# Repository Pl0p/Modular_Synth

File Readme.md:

# Welcome here =)

Here you can find all the resources I use to build my modules.
You will also find my modules, their Kicad files, their schematics as well as my sources of inspiration and pictures/videos of the prototypes and finished modules

You will also find

## [A big list of open-source/open-hardware builders](https://github.com/Pl0p/Modular_Synth/blob/main/List_of_open-source_makers.md)
All modules in the list are not necessarily in eurorack format, but all have their schematics available if not more

And 

### [A list (in progress) of modules by category](https://github.com/Pl0p/Modular_Synth/blob/main/List_of_modules_by_functions.md)
These are the module's files and descriptions available in the list above but classified by category

Don't hesitate to participate if you find other sources of music/video schematics

Thing you can do to help :
- Class thing in alphabetical order for the Open-hardware-builders list
- Add new entry
- Take a look at the modules by category and continue to class them
- Look for typos
- Have a good day =)

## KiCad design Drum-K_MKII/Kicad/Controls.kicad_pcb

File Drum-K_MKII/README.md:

# Drum K MkII
Analogue drum kick

## Controls are :

 - Transient shape
 - Decay
 - Tune
 - Tone
 - Distortion

### Inputs

 - Trigger
 - Decay CV (vactrol)
 - Accent

# [Here is the schematic](https://github.com/Pl0p/Modular_Synth/blob/main/Drum-K_MKII/Drum-K_MKII.pdf)

### Main PCB 

### Front Panel

### Sandwich

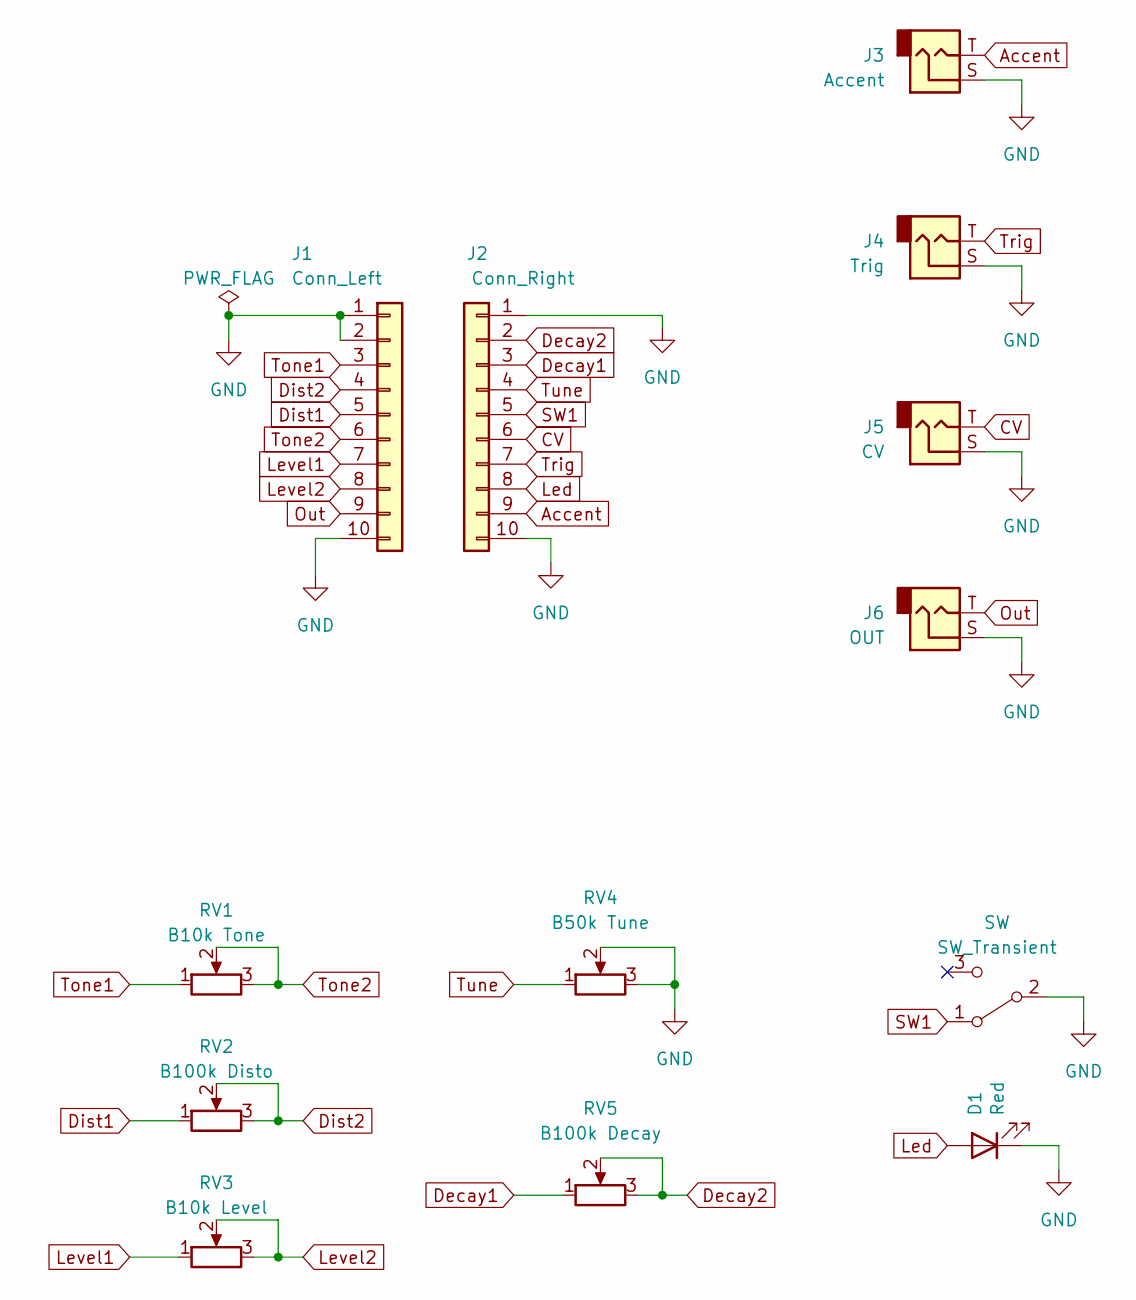
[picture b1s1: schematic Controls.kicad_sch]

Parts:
D1: Red; LED_D5.0mm
J1: Conn_Left; PinHeader_1x10
J2: Conn_Right; PinHeader_1x10
J3: Accent; Jack_3.5mm_Vertical
J4: Trig; Jack_3.5mm_Vertical
J5: CV; Jack_3.5mm_Vertical
J6: OUT; Jack_3.5mm_Vertical
RV1: B10k Tone; Potentiometer_Alps_RK09L_Single_Vertical
RV2: B100k Disto; Potentiometer_Alps_RK09L_Single_Vertical
RV3: B10k Level; Potentiometer_Alps_RK09L_Single_Vertical
RV4: B50k Tune; Potentiometer_Alps_RK09L_Single_Vertical
RV5: B100k Decay; Potentiometer_Alps_RK09L_Single_Vertical
SW: SW_Transient

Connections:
Accent: J2.9, J3.T
CV: J2.6, J5.T
Decay1: J2.3, RV5.1
Decay2: J2.2, RV5.2, RV5.3
Dist1: J1.5, RV2.1
Dist2: J1.4, RV2.2, RV2.3
GND: D1.1 (K), J1.1, J1.2, J1.10, J2.1, J2.10, J3.S, J4.S, J5.S, J6.S, RV4.2, RV4.3; also elsewhere on the board
Led: D1.2 (A), J2.8
Level1: J1.7, RV3.1
Level2: J1.8, RV3.2, RV3.3
Out: J1.9, J6.T
SW1: J2.5, J6.5, SW.1 (A); also elsewhere on the board
Tone1: J1.3, RV1.1
Tone2: J1.6, RV1.2, RV1.3
Trig: J2.7, J4.T
Tune: J2.4, RV4.1

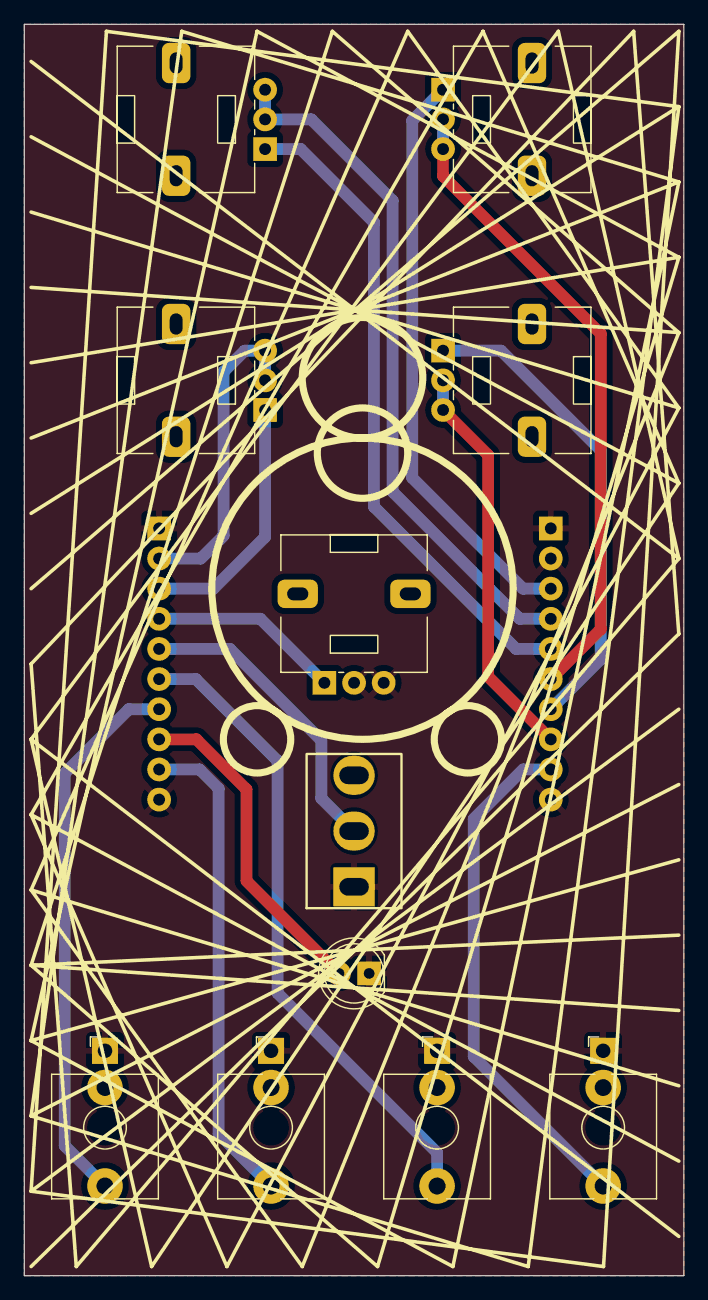
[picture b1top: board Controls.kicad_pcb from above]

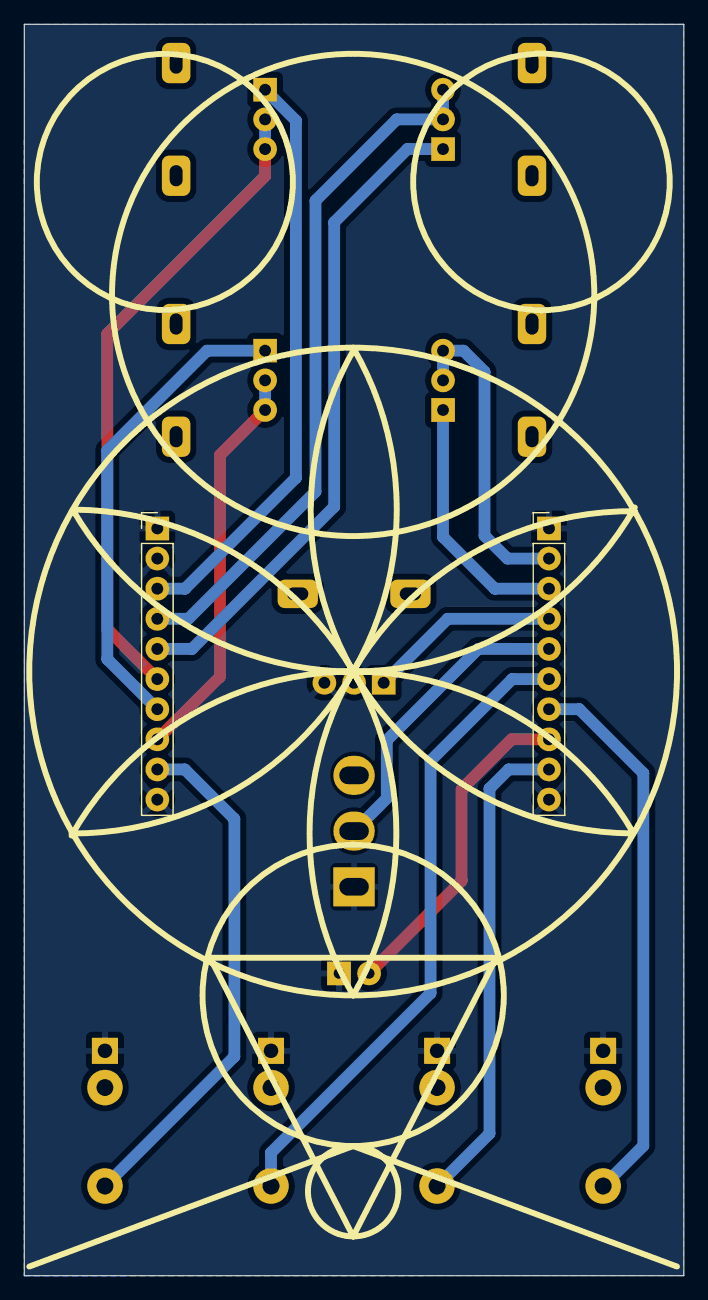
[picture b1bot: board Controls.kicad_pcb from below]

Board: 2 copper layers, 55.6 x 105.5 mm, 13 parts (2 on the bottom side), 16 nets.

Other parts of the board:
SW1: SW_Transient; Switch_MTS102

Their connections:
GND: SW1.1 (A); also elsewhere on the board
SW1: SW1.2 (B); also elsewhere on the board

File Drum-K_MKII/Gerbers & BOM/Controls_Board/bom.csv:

Designator,Footprint,Quantity,Value,LCSC Part #
D1,LED_D5.0mm,1,Red,
J1,PinHeader_1x10,1,Conn_Left,
J2,PinHeader_1x10,1,Conn_Right,
J3,Jack_3.5mm_Vertical,1,Accent,
J4,Jack_3.5mm_Vertical,1,Trig,
J5,Jack_3.5mm_Vertical,1,CV,
J6,Jack_3.5mm_Vertical,1,OUT,
RV1,Potentiometer_Alps_RK09L_Single_Vertical,1,B10k Tone,
RV2,Potentiometer_Alps_RK09L_Single_Vertical,1,B100k Disto,
RV3,Potentiometer_Alps_RK09L_Single_Vertical,1,B10k Level,
RV4,Potentiometer_Alps_RK09L_Single_Vertical,1,B50k Tune,
RV5,Potentiometer_Alps_RK09L_Single_Vertical,1,B100k Decay,
SW1,Switch_MTS102,1,SW_Transient,

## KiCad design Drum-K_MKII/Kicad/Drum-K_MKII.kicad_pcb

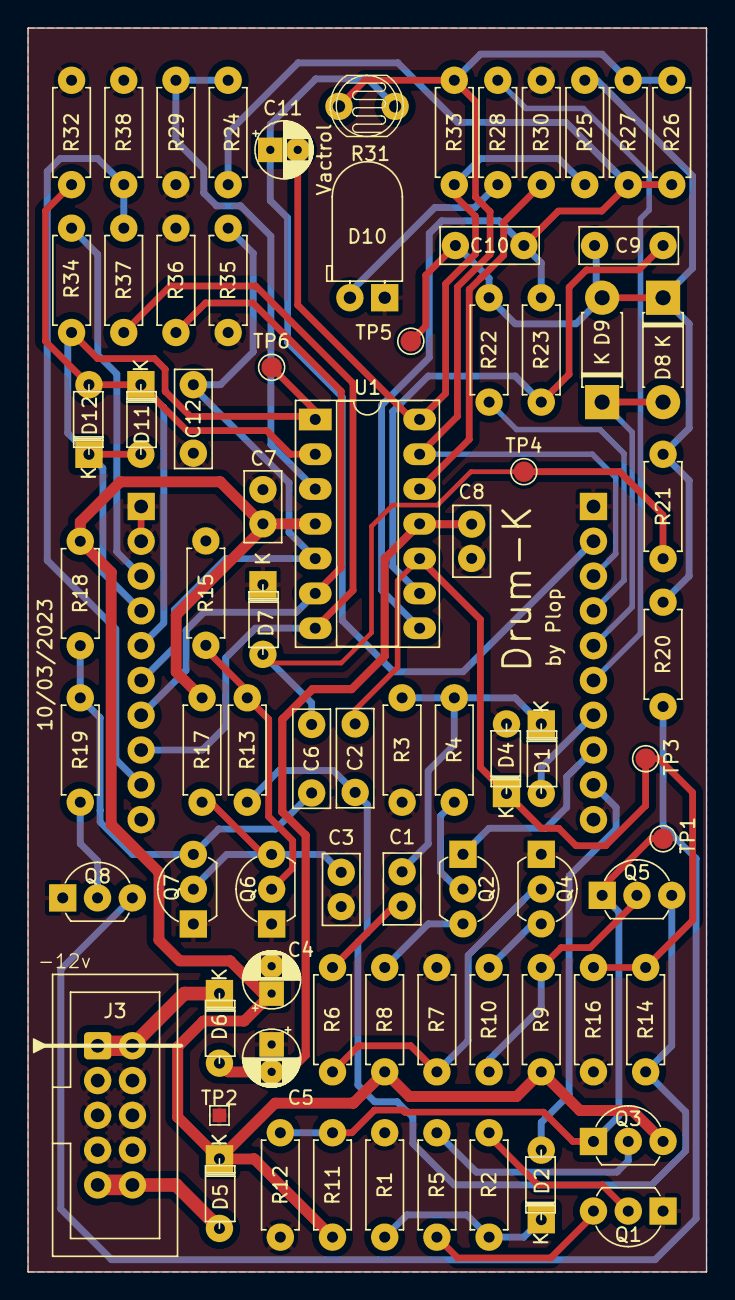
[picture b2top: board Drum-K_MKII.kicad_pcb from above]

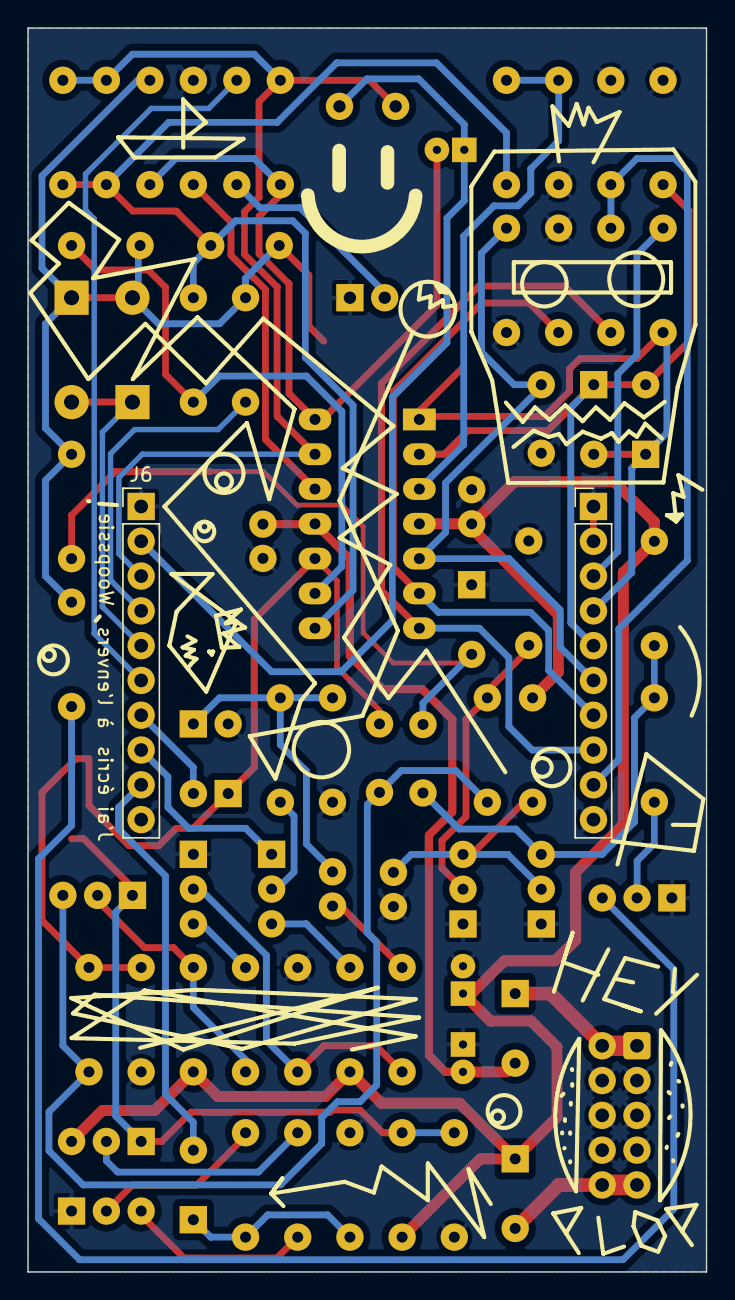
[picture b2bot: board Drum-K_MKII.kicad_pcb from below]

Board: 2 copper layers, 49.5 x 90.8 mm, 79 parts (2 on the bottom side), 47 nets.

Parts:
C1, C3: 100n; C_Disc_D5.0mm_W2.5mm_P2.50mm
C2: 10n; C_Rect_L7.0mm_W2.5mm_P5.00mm
C4, C5: 10uf; CP_Radial_D4.0mm_P2.00mm
C6: 33nf; C_Rect_L7.0mm_W2.5mm_P5.00mm
C7, C8: 100nf; C_Disc_D5.0mm_W2.5mm_P2.50mm
C9, C10: 56nf; C_Rect_L7.0mm_W2.5mm_P5.00mm
C11: 33uf; CP_Radial_D4.0mm_P2.00mm
C12: 100nf; C_Rect_L7.0mm_W2.5mm_P5.00mm
D1, D2, D4, D5, D6, D7, D11, D12: 1N4148; DO-35_SOD27_P5.08mm_Horizontal
D8, D9: 1N4007; DO-41_SOD81_P7.62mm_Horizontal(1n4007)
D10: LED White; LED_D5.0mm_Horizontal
J3: Eurorack_power; IDC-Header_2x05
J5: Conn_Left; PinHeader_1x10
J6: Conn_Right; PinHeader_1x10
Q1, Q2, Q4, Q6, Q7, Q8: 2N3904; TO-92L_Inline_Wide
Q3, Q5: 2N3906; TO-92L_Inline_Wide
R1, R3, R4, R5, R14, R19, R28, R35, R38: 100k; Resistor_D2.5mm_P7.62mm
R2, R7, R10, R29: 10k; Resistor_D2.5mm_P7.62mm
R6, R18, R30: 20k; Resistor_D2.5mm_P7.62mm
R8, R9, R13, R16, R22: 4.7k; Resistor_D2.5mm_P7.62mm
R11, R32, R36, R37: 1k; Resistor_D2.5mm_P7.62mm
R12, R17, R21, R23: 1M; Resistor_D2.5mm_P7.62mm
R15: 2.2k; Resistor_D2.5mm_P7.62mm
R20: 6.8; Resistor_D2.5mm_P7.62mm
R24: 51k; Resistor_D2.5mm_P7.62mm
R25, R26: 470k; Resistor_D2.5mm_P7.62mm
R27, R33: 47k; Resistor_D2.5mm_P7.62mm
R31: 5537; LDR_D5.0mm
R34: 100; Resistor_D2.5mm_P7.62mm
TP1, TP3, TP4, TP5, TP6: TestPoint; TestPoint_Round
TP2: TestPoint; TestPoint_square
U1: TL074; DIP-14_W7.62mm_Socket_LongPads

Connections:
+12V: C4.1, C7.1, D5.1 (K), Q3.3 (C), R8.2, R9.1, R11.1, R17.1, R18.1, U1.4 (V+)
-12V: C5.2, C8.2, D6.2 (A), U1.11 (V-)
Accent: D2.2 (A), J6.9
CV: J6.6, R28.1
Decay1: J6.3, R26.2, R27.2, R31.2, R33.1, U1.13 (-)
Decay2: C11.1, J6.2, R31.1
Dist1: D11.1 (K), D12.2 (A), J5.5, R32.2, U1.2 (-)
Dist2: D11.2 (A), D12.1 (K), J5.4, R34.1, TP6.1, U1.1
GND: C3.2, C4.2, C5.1, C7.2, C8.1, C12.2, D4.2 (A), D7.1 (K), D10.1 (K), J3.3, J3.4, J3.5, J3.6, J3.7, J3.8, J5.1, J5.2, J5.10, J6.1, J6.10, Q1.1 (E), Q4.1 (E), Q6.1 (E), Q7.1 (E), Q8.1 (E), R1.2, R3.2, R7.2, R12.2, R15.1, R16.1, R29.1, R30.1, R32.1, R35.2, R36.2, R38.2, TP2.1
Led: J6.8, Q2.1 (E)
Level1: J5.7, R36.1, U1.6 (-)
Level2: J5.8, R37.2, U1.7
unnamed: C1.2, R6.1
unnamed: C10.2, R23.1, R24.1, R26.1, R27.1, U1.8
unnamed: C11.2, R25.2, R33.2, U1.14
unnamed: C1.1, D1.1 (K), R3.1, R4.2
unnamed: D2.1 (K), R1.1, R2.1
unnamed: C2.2, D4.1 (K), R14.2, R16.2, TP3.1, U1.10 (+)
unnamed: D5.2 (A), J3.9, J3.10
unnamed: D6.1 (K), J3.1, J3.2
unnamed: C6.2, D7.2 (A), R21.1, TP4.1
unnamed: C9.2, C10.1, D8.1 (K), D9.2 (A), R20.2, R21.2, R22.1, R25.1, TP5.1
unnamed: D10.2 (A), R28.2
unnamed: Q1.2 (B), R2.2
unnamed: Q1.3 (C), R5.1
unnamed: Q2.2 (B), R4.1
unnamed: Q2.3 (C), R8.1
unnamed: Q3.2 (B), R5.2
unnamed: Q3.1 (E), Q5.1 (E), R11.2, R12.1, TP1.1
unnamed: Q4.2 (B), R6.2, R7.1
unnamed: Q4.3 (C), R10.2
unnamed: Q5.2 (B), R9.2, R10.1
unnamed: C2.1, Q5.3 (C), R13.1, R14.1
unnamed: Q6.2 (B), R13.2, R15.2
unnamed: C3.1, Q6.3 (C), Q7.2 (B), R17.2
unnamed: C6.1, Q7.3 (C), R18.2, R19.1
unnamed: Q8.2 (B), R19.2
unnamed: Q8.3 (C), R20.1
unnamed: R24.2, R29.2, U1.3 (+)
unnamed: C9.1, R23.2, U1.9 (-)
unnamed: R30.2, U1.12 (+)
Out: J5.9, R37.1, R38.1
SW1: D8.2 (A), D9.1 (K), J6.5
Tone1: J5.3, R34.2
Tone2: C12.1, J5.6, R35.1, U1.5 (+)
Trig: D1.2 (A), J6.7
Tune: J6.4, R22.2

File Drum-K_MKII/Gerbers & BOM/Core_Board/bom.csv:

Designator,Footprint,Quantity,Value,LCSC Part #
"C1, C3",C_Disc_D5.0mm_W2.5mm_P2.50mm,2,100n,
"C10, C9",C_Rect_L7.0mm_W2.5mm_P5.00mm,2,56nf,
C11,CP_Radial_D4.0mm_P2.00mm,1,33uf,
C12,C_Rect_L7.0mm_W2.5mm_P5.00mm,1,100nf,
C2,C_Rect_L7.0mm_W2.5mm_P5.00mm,1,10n,
"C4, C5",CP_Radial_D4.0mm_P2.00mm,2,10uf,
C6,C_Rect_L7.0mm_W2.5mm_P5.00mm,1,33nf,
"C7, C8",C_Disc_D5.0mm_W2.5mm_P2.50mm,2,100nf,
"D1, D11, D12, D2, D4, D5, D6, D7",DO-35_SOD27_P5.08mm_Horizontal,8,1N4148,
D10,LED_D5.0mm_Horizontal,1,LED White,
"D8, D9",DO-41_SOD81_P7.62mm_Horizontal(1n4007),2,1N4007,
J3,IDC-Header_2x05,1,Eurorack_power,
J5,PinHeader_1x10,1,Conn_Left,
J6,PinHeader_1x10,1,Conn_Right,
"Q1, Q2, Q4, Q6, Q7, Q8",TO-92L_Inline_Wide,6,2N3904,
"Q3, Q5",TO-92L_Inline_Wide,2,2N3906,
"R1, R14, R19, R28, R3, R35, R38, R4, R5",Resistor_D2.5mm_P7.62mm,9,100k,
"R10, R2, R29, R7",Resistor_D2.5mm_P7.62mm,4,10k,
"R11, R32, R36, R37",Resistor_D2.5mm_P7.62mm,4,1k,
"R12, R17, R21, R23",Resistor_D2.5mm_P7.62mm,4,1M,
"R13, R16, R22, R8, R9",Resistor_D2.5mm_P7.62mm,5,4.7k,
R15,Resistor_D2.5mm_P7.62mm,1,2.2k,
"R18, R30, R6",Resistor_D2.5mm_P7.62mm,3,20k,
R20,Resistor_D2.5mm_P7.62mm,1,6.8,
R24,Resistor_D2.5mm_P7.62mm,1,51k,
"R25, R26",Resistor_D2.5mm_P7.62mm,2,470k,
"R27, R33",Resistor_D2.5mm_P7.62mm,2,47k,
R31,LDR_D5.0mm,1,5537,
R34,Resistor_D2.5mm_P7.62mm,1,100,
"TP1, TP3, TP4, TP5, TP6",TestPoint_Round,5,TestPoint,
TP2,TestPoint_square,1,TestPoint,
U1,DIP-14_W7.62mm_Socket_LongPads,1,TL074,

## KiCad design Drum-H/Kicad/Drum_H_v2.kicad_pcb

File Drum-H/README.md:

# Drum_H Hi Hats

    ( /!\ NOT TESTED /!\ ) 

This is the third module I've done, i'm curently soldering =)

    ( /!\ NOT TESTED /!\ )

Independant output for the open hat and the closed hat

## Controls are :

 - Open hat Decay
 - Open hat Volume
 - Closed hat Decay
 - Closed hat Volume
 - White noise / Metal noise MIX
 - White noise tone
 - Metal Caracter
 - Metal Tune
 - Interaction between Open/Closed hat (if switch ON, the Closed hat will cancel the open one (like a real one)

### Inputs

 - Open hat Trigger
 - Closed hat Trigger
 - [ ] Open hat Decay CV
 - [ ] Closed hat Decay CV

# [Here is the schematic](https://github.com/Pl0p/Modular_Synth/blob/main/Drum-H/Drum_H_v2.pdf)

### Front of the PCB 

### Back of the PCB

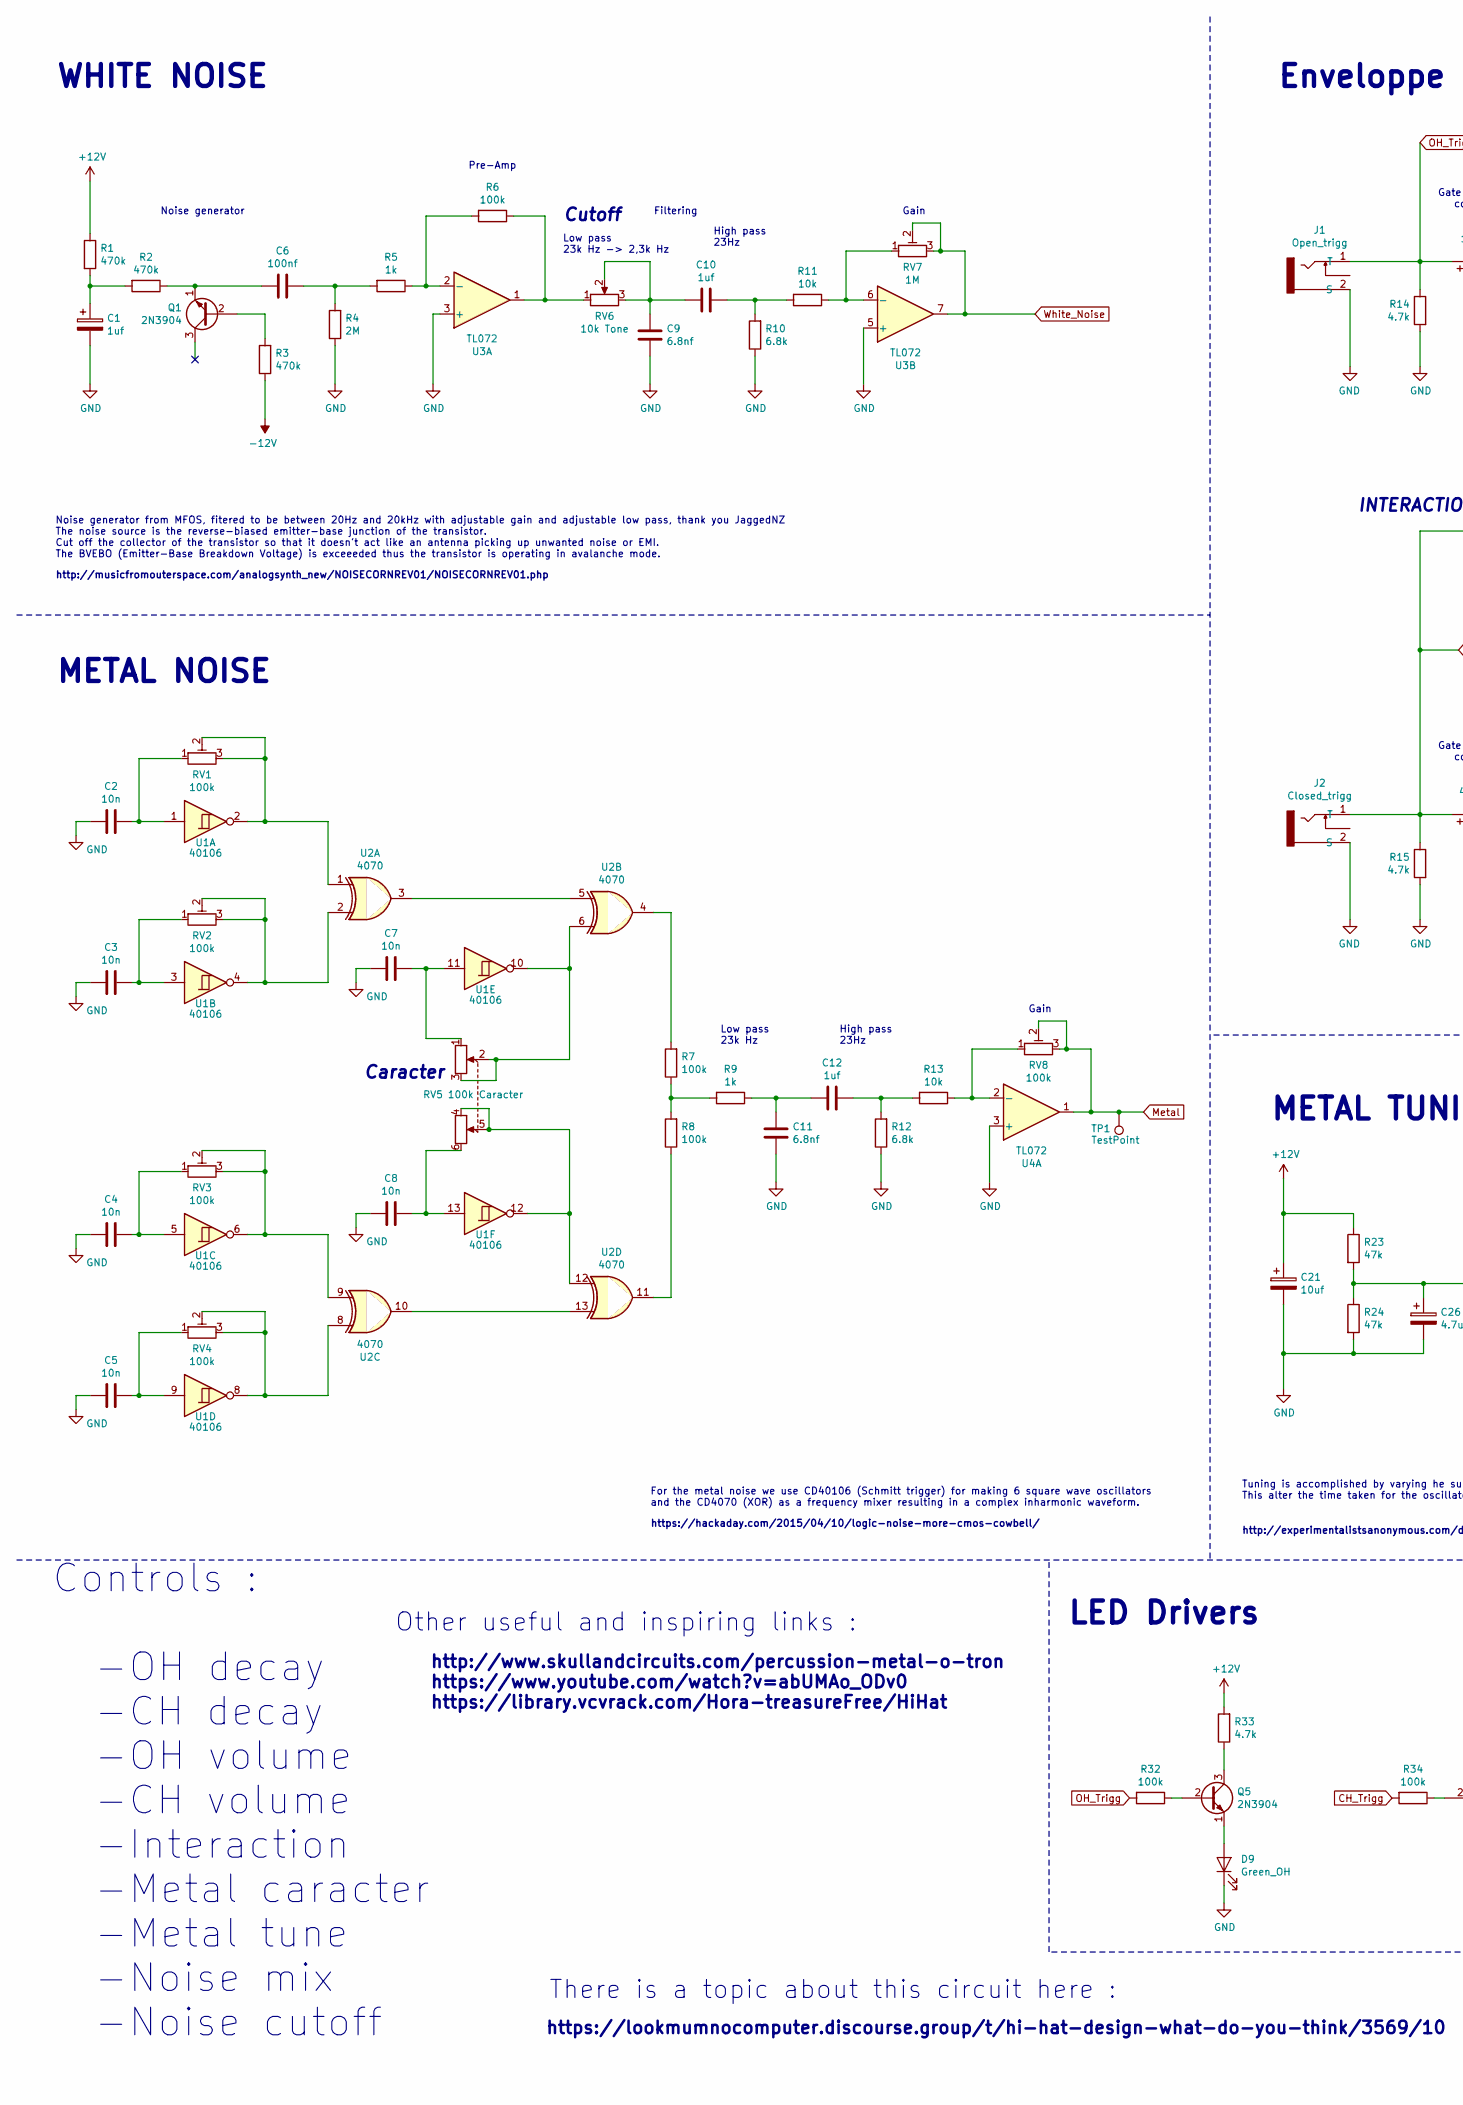
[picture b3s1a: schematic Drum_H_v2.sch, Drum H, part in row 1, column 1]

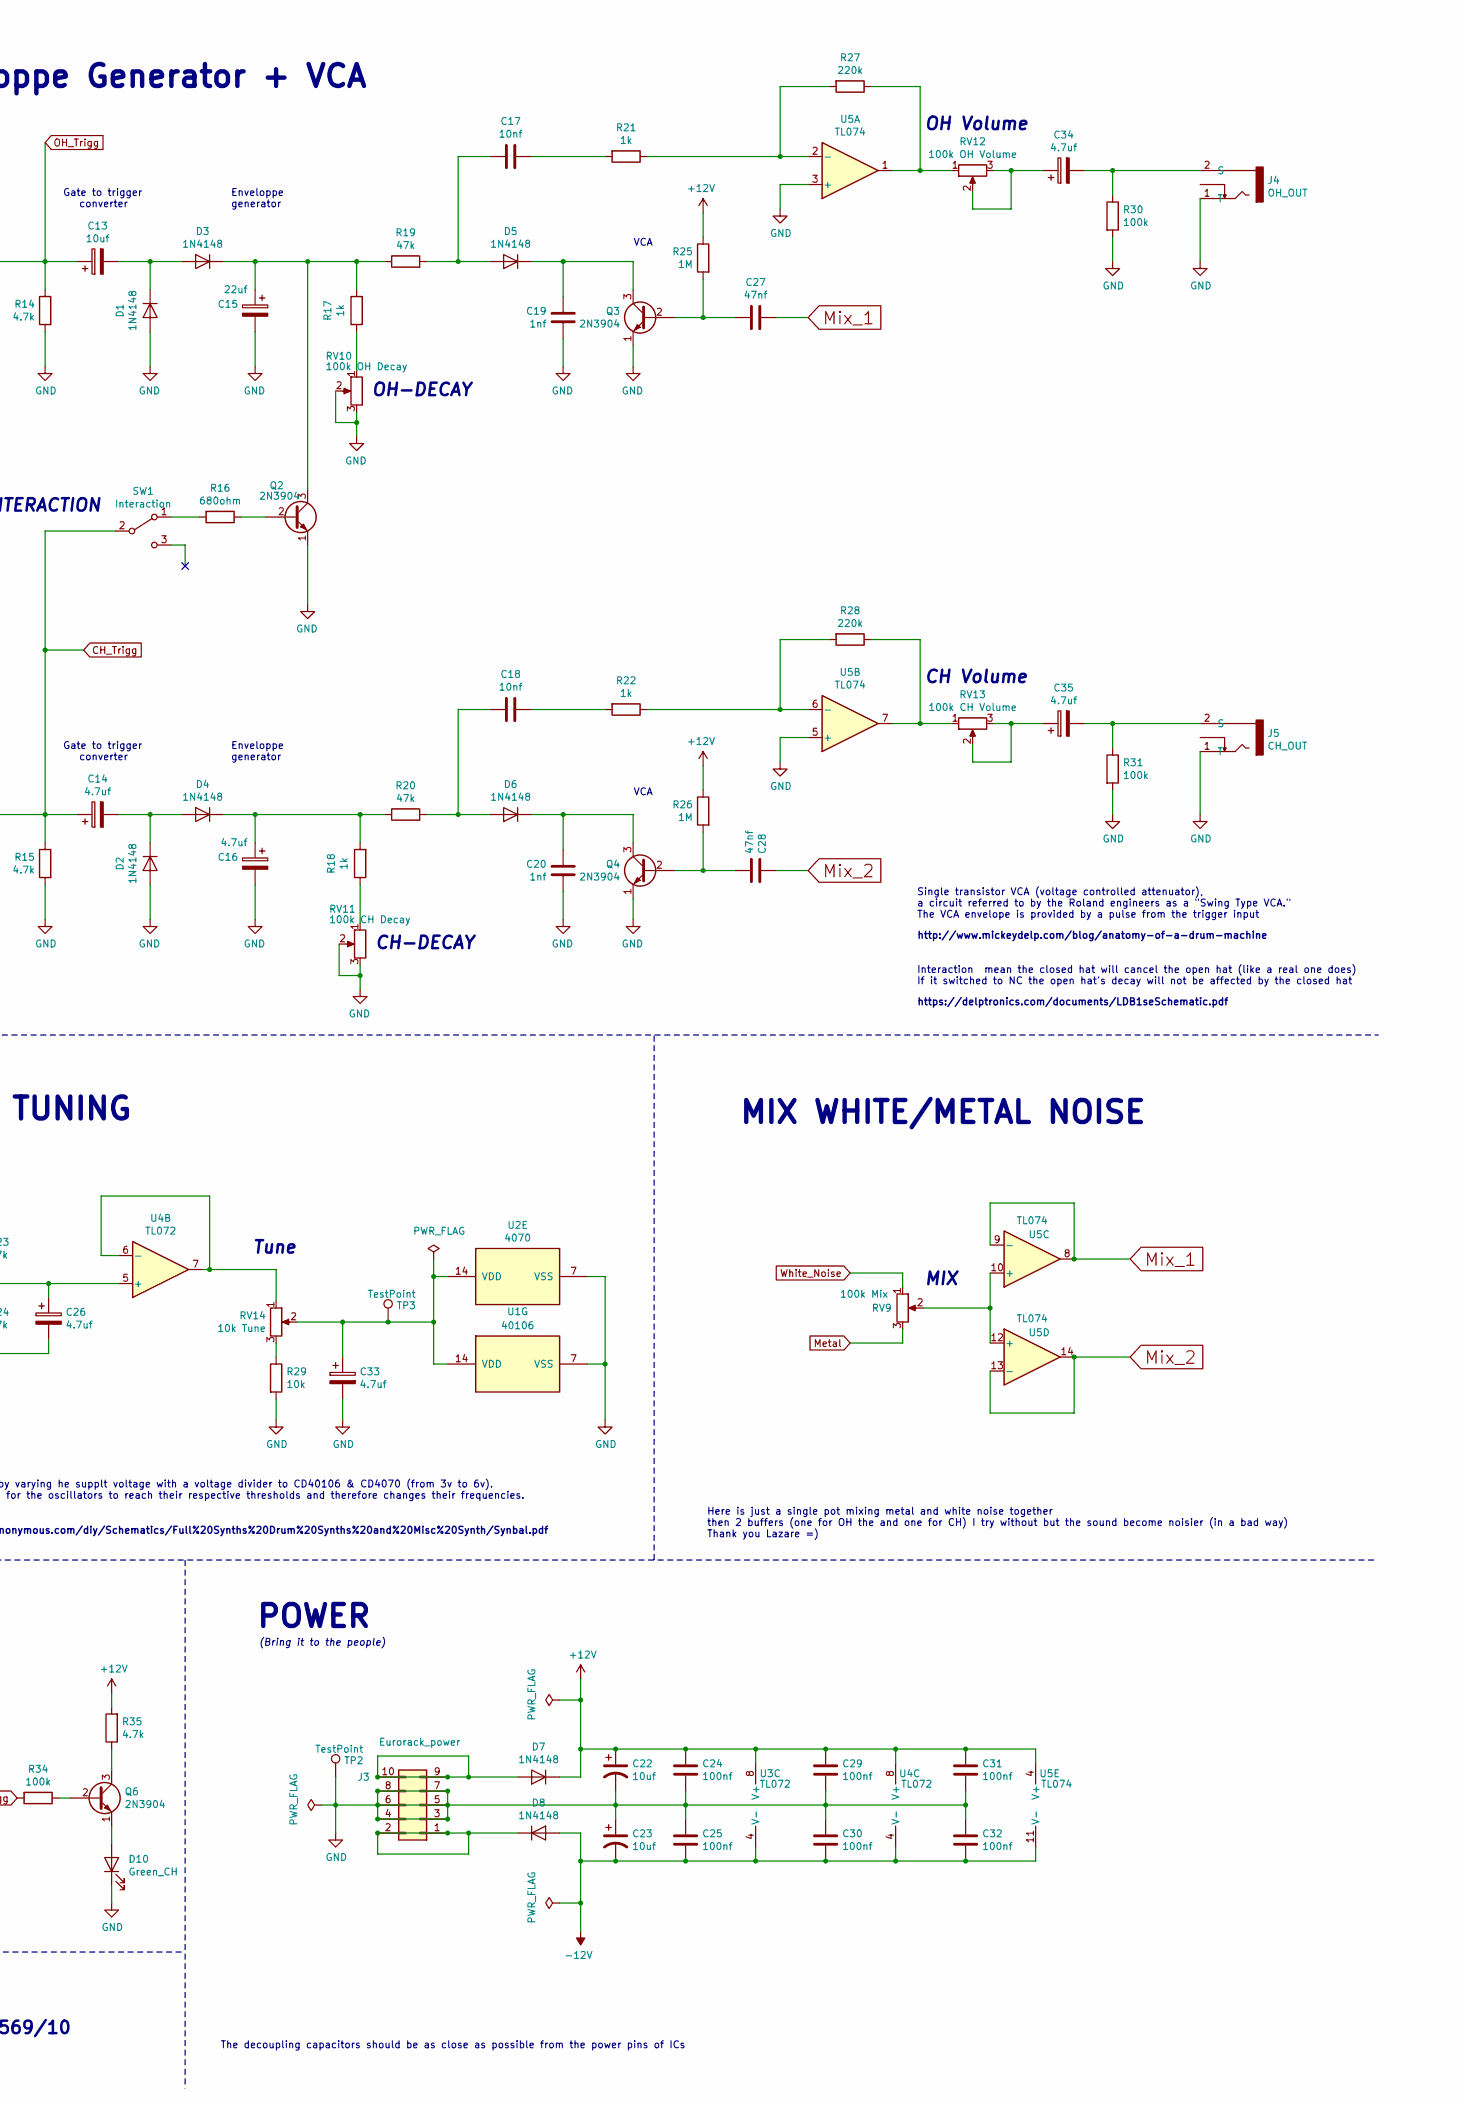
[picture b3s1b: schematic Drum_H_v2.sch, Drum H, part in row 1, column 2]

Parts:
C1: 1uf; CP_Radial_5*11
C2, C3, C4, C5, C7, C8: 10n; C_Ceramic_Disc
C6, C24, C25, C29, C30, C31, C32: 100nf; C_Ceramic_Disc
C9, C11: 6.8nf; C_Ceramic_Disc
C10, C12: 1uf; C_Rect_1uf_(grey)
C13: 10uf; CP_Radial_4*7
C14, C16, C26, C33, C34, C35: 4.7uf; CP_Radial_4*7
C15: 22uf; CP_Radial_4*7
C17, C18: 10nf; C_Ceramic_Disc
C19, C20: 1nf; C_Ceramic_Disc
C21, C22, C23: 10uf; CP_Radial_5*11
C27, C28: 47nf; C_Ceramic_Disc
D1, D2, D3, D4, D5, D6, D7, D8: 1N4148; Diode_1N4148
D9: Green_OH; LED_5.0mm
D10: Green_CH; LED_5.0mm
J1: Open_trigg; Wire_Pad_1x02_(1Nc)_Drill-1.5mm
J2: Closed_trigg; Wire_Pad_1x02_(1Nc)_Drill-1.5mm
J3: Eurorack_power; 2X05_Power_conn
J4: OH_OUT; Wire_Pad_1x02_(1Nc)_Drill-1.5mm
J5: CH_OUT; Wire_Pad_1x02_(1Nc)_Drill-1.5mm
Q1, Q2, Q3, Q4, Q5, Q6: 2N3904; TO-92_Inline
R1, R2, R3: 470k; Resistor
R4: 2M; Resistor
R5, R9, R17, R18, R21, R22: 1k; Resistor
R6, R7, R8, R30, R31, R32, R34: 100k; Resistor
R10, R12: 6.8k; Resistor
R11, R13, R29: 10k; Resistor
R14, R15, R33, R35: 4.7k; Resistor
R16: 680ohm; Resistor
R19, R20, R23, R24: 47k; Resistor
R25, R26: 1M; Resistor
R27, R28: 220k; Resistor
RV1, RV2, RV3, RV4, RV8: 100k; Trimot_RM-065
RV5: 100k Caracter; Wire_Pad_2x03_(2Nc)_Drill-1.5mm
RV6: 10k Tone; Wire_Pad_1x03_(1Nc)_Drill-1.5mm
RV7: 1M; Trimot_RM-065
RV9: 100k Mix; Wire_Pad_1x03_Drill-1.5mm
RV10: 100k OH Decay; Wire_Pad_1x03_(2Nc)_Drill-1.5mm
RV11: 100k CH Decay; Wire_Pad_1x03_(2Nc)_Drill-1.5mm
RV12: 100k OH Volume; Wire_Pad_1x03_(1Nc)_Drill-1.5mm
RV13: 100k CH Volume; Wire_Pad_1x03_(1Nc)_Drill-1.5mm
RV14: 10k Tune; Wire_Pad_1x03_Drill-1.5mm
SW1: Interaction; Wire_Pad_1x03_(1Nc)_Drill-1.5mm
TP1, TP2, TP3: TestPoint; Test-Point_3x3
U1: 40106; DIP-14-Socket
U2: 4070; DIP-14-Socket
U3, U4: TL072; DIP-8_Socket
U5: TL074; DIP-14-Socket

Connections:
+12V: C21.1, C22.1, C24.1, C29.1, C31.1, D7.1 (K), R1.1, R23.1, R25.1, R26.1, R33.2, R35.2, U3.8 (V+), U4.8 (V+), U5.4 (V+)
-12V: C23.2, C25.2, C30.2, C32.2, D8.2 (A), R3.1, U3.4 (V-), U4.4 (V-), U5.11 (V-)
CH_Trigg: C14.1, J2.1 (T), R15.1, R34.2, SW1.2 (B)
GND: C1.2, C2.2, C3.2, C4.2, C5.2, C7.2, C8.2, C9.2, C11.2, C15.2, C16.2, C19.2, C20.2, C21.2, C22.2, C23.1, C24.2, C25.1, C26.2, C29.2, C30.1, C31.2, C32.1, C33.2, D1.2 (A), D2.2 (A), D9.1 (K), D10.1 (K), J1.2 (S), J2.2 (S), J3.3, J3.4, J3.5, J3.6, J3.7, J3.8, J4.1 (T), J5.1 (T), Q2.1 (E), Q3.1 (E), Q4.1 (E), R4.1, R10.1, R12.1, R14.2, R15.2, R24.2, R29.2, R30.2, R31.2, RV10.2, RV10.3, RV11.2, RV11.3, TP2.1, U1.7 (VSS), U2.7 (VSS), U3.3 (+), U3.5 (+), U4.3 (+), U5.3 (+), U5.5 (+)
Metal: RV8.2, RV8.3, RV9.3, TP1.1, U4.1; also elsewhere on the board
Mix_1: C27.2, U5.8, U5.9 (-)
Mix_2: C28.1, U5.13 (-), U5.14
unnamed: C1.1, R1.2, R2.2
unnamed: C2.1, RV1.1, U1.1
unnamed: C3.1, RV2.1, U1.3
unnamed: C4.1, RV3.1, U1.5
unnamed: C5.1, RV4.1, U1.9
unnamed: C6.1, R4.2, R5.2
unnamed: C6.2, Q1.1 (E), R2.1
unnamed 14: C7.1, RV5.1, U1.11; also elsewhere on the board
unnamed 15: C8.1, RV5.6, U1.13; also elsewhere on the board
unnamed: C10.1, R10.2, R11.2
unnamed 17: C9.1, C10.2, RV6.2, RV6.3; also elsewhere on the board
unnamed: C11.1, C12.2, R9.1
unnamed: C12.1, R12.2, R13.2
unnamed: C13.2, D1.1 (K), D3.2 (A)
unnamed: C14.2, D2.1 (K), D4.2 (A)
unnamed: C15.1, D3.1 (K), Q2.3 (C), R17.2, R19.1
unnamed: C16.1, D4.1 (K), R18.2, R20.1
unnamed: C17.1, R21.2
unnamed: C17.2, D5.2 (A), R19.2
unnamed: C18.1, R22.2
unnamed: C18.2, D6.2 (A), R20.2
unnamed: C19.1, D5.1 (K), Q3.3 (C)
unnamed: C20.1, D6.1 (K), Q4.3 (C)
unnamed: C26.1, R23.2, R24.1, U4.5 (+)
unnamed: C27.1, Q3.2 (B), R25.2
unnamed: C28.2, Q4.2 (B), R26.2
unnamed 33: C33.1, RV14.2, TP3.1, U1.14 (VDD), U2.14 (VDD); also elsewhere on the board
unnamed 34: C34.1, RV12.2, RV12.3; also elsewhere on the board
unnamed: C34.2, J4.2 (S), R30.1
unnamed 36: C35.1, RV13.2, RV13.3; also elsewhere on the board
unnamed: C35.2, J5.2 (S), R31.1
unnamed: D7.2 (A), J3.9, J3.10
unnamed: D8.1 (K), J3.1, J3.2
unnamed 40: D9.2 (A), Q5.1 (E); also elsewhere on the board
unnamed 41: D10.2 (A), Q6.1 (E); also elsewhere on the board
unnamed: Q1.2 (B), R3.2
unnamed: Q2.2 (B), R16.1
unnamed: Q5.2 (B), R32.1
unnamed: Q5.3 (C), R33.1
unnamed: Q6.2 (B), R34.1
unnamed: Q6.3 (C), R35.1
unnamed: R5.1, R6.2, U3.2 (-)
unnamed 50: R6.1, RV6.1, U3.1; also elsewhere on the board
unnamed: R7.1, R8.2, R9.2
unnamed: R7.2, U2.4
unnamed: R8.1, U2.11
unnamed: R11.1, RV7.1, U3.6 (-)
unnamed: R13.1, RV8.1, U4.2 (-)
unnamed: R16.2, SW1.1 (A)
unnamed 57: R17.1, RV10.1; also elsewhere on the board
unnamed 58: R18.1, RV11.1; also elsewhere on the board
unnamed: R21.1, R27.2, U5.2 (-)
unnamed: R22.1, R28.2, U5.6 (-)
unnamed 61: R27.1, RV12.1, U5.1; also elsewhere on the board
unnamed 62: R28.1, RV13.1, U5.7; also elsewhere on the board
unnamed 63: R29.1, RV14.3; also elsewhere on the board
unnamed: RV1.2, RV1.3, U1.2, U2.1
unnamed: RV2.2, RV2.3, U1.4, U2.2
unnamed: RV3.2, RV3.3, U1.6, U2.9
unnamed: RV4.2, RV4.3, U1.8, U2.8
unnamed 68: RV5.2, RV5.3, U1.10, U2.6; also elsewhere on the board
unnamed 69: RV5.4, RV5.5, U1.12, U2.12; also elsewhere on the board
unnamed 70: RV9.2, U5.10 (+), U5.12 (+); also elsewhere on the board
unnamed 71: RV14.1, U4.6 (-), U4.7; also elsewhere on the board
unnamed: U2.3, U2.5
unnamed: U2.10, U2.13
OH_Trigg: C13.1, J1.1 (T), R14.1, R32.2
White_Noise: RV7.2, RV7.3, RV9.1, U3.7; also elsewhere on the board

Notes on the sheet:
METAL NOISE
MIX WHITE/METAL NOISE
Gate to trigger converter
OH-DECAY
Enveloppe Generator + VCA
CH-DECAY
WHITE NOISE
Filtering
High pass 23Hz
Low pass 23k Hz -> 2,3k Hz
Pre-Amp
Noise generator
Gain
MIX
VCA
Enveloppe generator
OH Volume
CH Volume
Controls : -OH decay -CH decay -OH volume -CH volume -Interaction -Metal caracter -Metal tune -Noise mix -Noise cutoff
Tune
METAL TUNING
Caracter
Low pass 23k Hz
Here is just a single pot mixing metal and white noise together then 2 buffers (one for OH the and one for CH) I try without but the sound become noisier (in a bad way) Thank you Lazare =)
Tuning is accomplished by varying he supplt voltage with a voltage divider to CD40106 & CD4070 (from 3v to 6v). This alter the time taken for the oscillators to reach their respective thresholds and therefore changes their frequencies.
http://experimentalistsanonymous.com/diy/Schematics/Full%20Synths%20Drum%20Synths%20and%20Misc%20Synth/Synbal.pdf
Noise generator from MFOS, fitered to be between 20Hz and 20kHz with adjustable gain and adjustable low pass, thank you JaggedNZ The noise source is the reverse-biased emitter-base junction of the transistor. Cut off the collector of the transistor so that it doesn't act like an antenna picking up 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
http://musicfromouterspace.com/analogsynth_new/NOISECORNREV01/NOISECORNREV01.php
For the metal noise we use CD40106 (Schmitt trigger) for making 6 square wave oscillators and the CD4070 (XOR) as a frequency mixer resulting in a complex inharmonic waveform.
https://hackaday.com/2015/04/10/logic-noise-more-cmos-cowbell/
Single transistor VCA (voltage controlled attenuator), a circuit referred to by the Roland engineers as a "Swing Type VCA." The VCA envelope is provided by a pulse from the trigger input
http://www.mickeydelp.com/blog/anatomy-of-a-drum-machine
POWER
The decoupling capacitors should be as close as possible from the power pins of ICs
Other useful and inspiring links :
http://www.skullandcircuits.com/percussion-metal-o-tron https://www.youtube.com/watch?v=abUMAo_ODv0 https://library.vcvrack.com/Hora-treasureFree/HiHat
Cutoff
Interaction mean the closed hat will cancel the open hat (like a real one does) If it switched to NC the open hat's decay will not be affected by the closed hat
https://delptronics.com/documents/LDB1seSchematic.pdf
INTERACTION

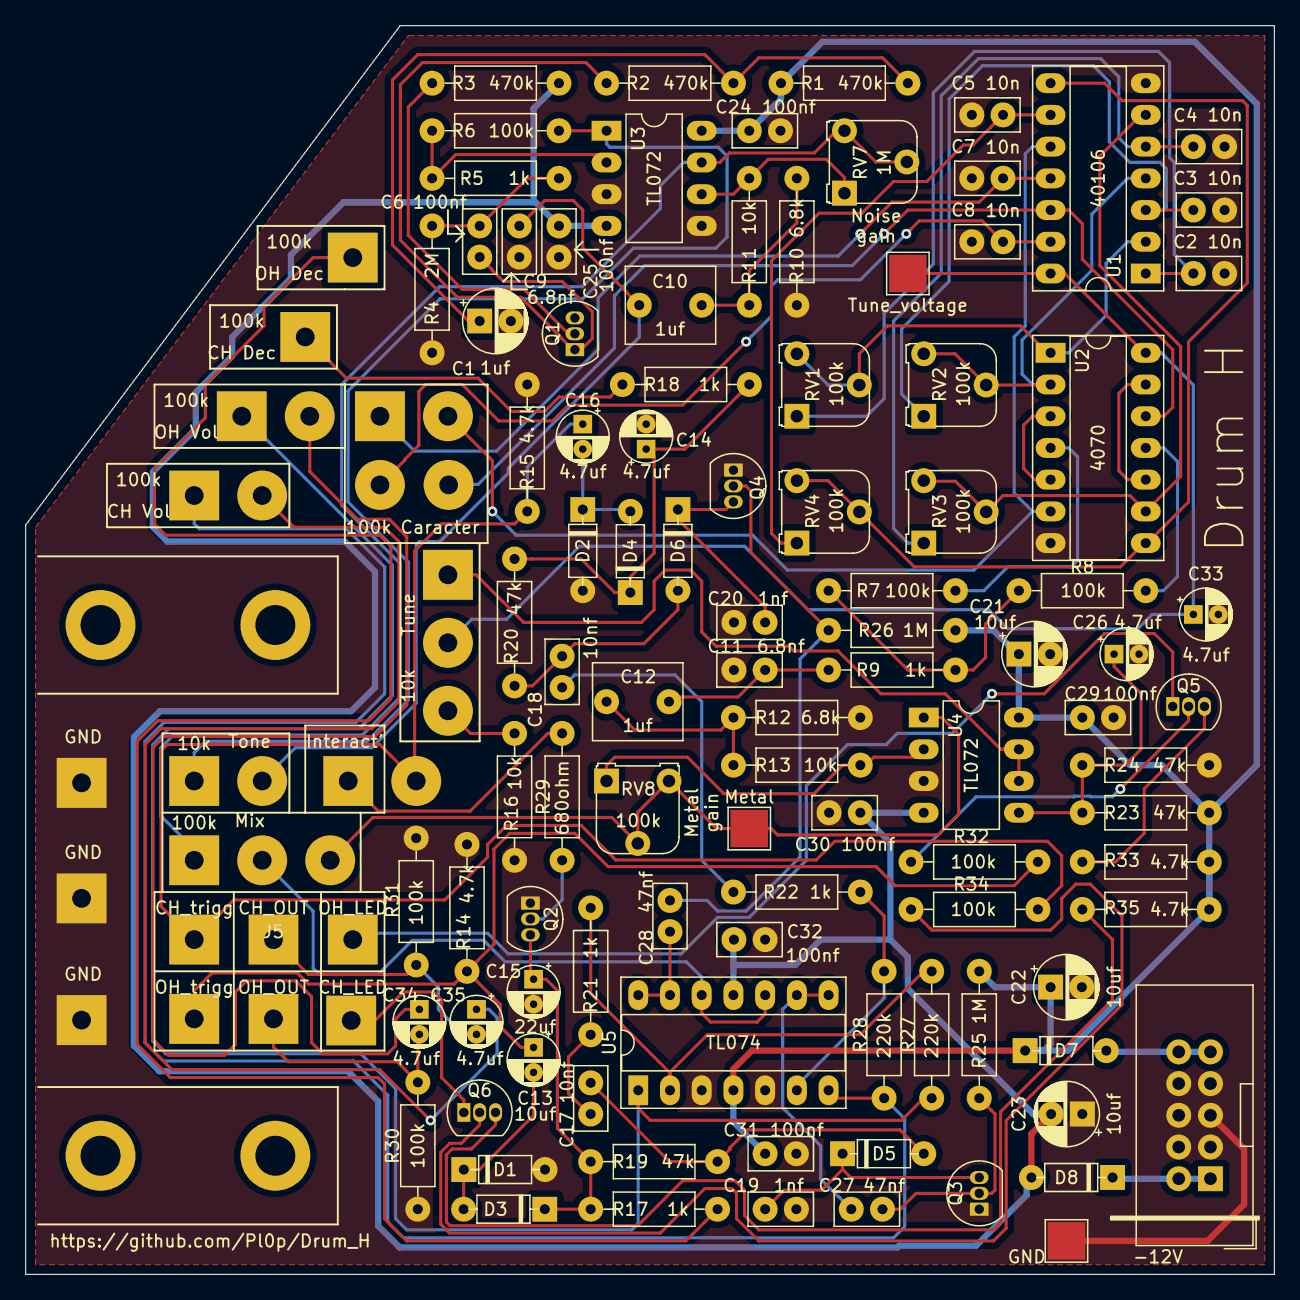
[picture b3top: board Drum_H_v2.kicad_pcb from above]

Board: 2 copper layers, 100.0 x 100.0 mm, 114 parts (0 on the bottom side), 75 nets.

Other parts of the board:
10k: Tone; Wire_Pad_1x03_(1Nc)_Drill-1.5mm
10k#2: Tune; Wire_Pad_1x03_Drill-1.5mm
100k: Mix; Wire_Pad_1x03_Drill-1.5mm
100k#2: Caracter; Wire_Pad_2x03_(2Nc)_Drill-1.5mm
100k#3: CH Dec; Wire_Pad_1x03_(2Nc)_Drill-1.5mm
100k#4: CH Vol; Wire_Pad_1x03_(1Nc)_Drill-1.5mm
100k#5: OH Vol; Wire_Pad_1x03_(1Nc)_Drill-1.5mm
CH_LED: Green; Wire_Pad_1x02_(1Nc)_Drill-1.5mm
OH Dec: 100k; Wire_Pad_1x03_(2Nc)_Drill-1.5mm
OH_LED: Green; Wire_Pad_1x02_(1Nc)_Drill-1.5mm

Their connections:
Metal: 100k.3; also elsewhere on the board
unnamed 14: 100k#2.1; also elsewhere on the board
unnamed 15: 100k#2.6; also elsewhere on the board
unnamed 17: 10k.3; also elsewhere on the board
unnamed 33: 10k#2.2; also elsewhere on the board
unnamed 34: 100k#5.2; also elsewhere on the board
unnamed 36: 100k#4.2; also elsewhere on the board
unnamed 40: OH_LED.1; also elsewhere on the board
unnamed 41: CH_LED.2; also elsewhere on the board
unnamed 50: 10k.1; also elsewhere on the board
unnamed 57: OH Dec.1; also elsewhere on the board
unnamed 58: 100k#3.1; also elsewhere on the board
unnamed 61: 100k#5.1; also elsewhere on the board
unnamed 62: 100k#4.1; also elsewhere on the board
unnamed 63: 10k#2.3; also elsewhere on the board
unnamed 68: 100k#2.2; also elsewhere on the board
unnamed 69: 100k#2.5; also elsewhere on the board
unnamed 70: 100k.2; also elsewhere on the board
unnamed 71: 10k#2.1; also elsewhere on the board
White_Noise: 100k.1; also elsewhere on the board
